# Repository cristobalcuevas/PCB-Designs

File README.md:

<!-- boardrepo-badge:v1 -->

<!-- /boardrepo-badge:v1 -->

# Kicad
Projects with Kicad

### [HornSystem](/HornSystem)

### [LoRaPill](/LoRaPill)

### [PIC18F4550](/PIC18F4550)

### [Shield ESP32](/Shield%20ESP32)

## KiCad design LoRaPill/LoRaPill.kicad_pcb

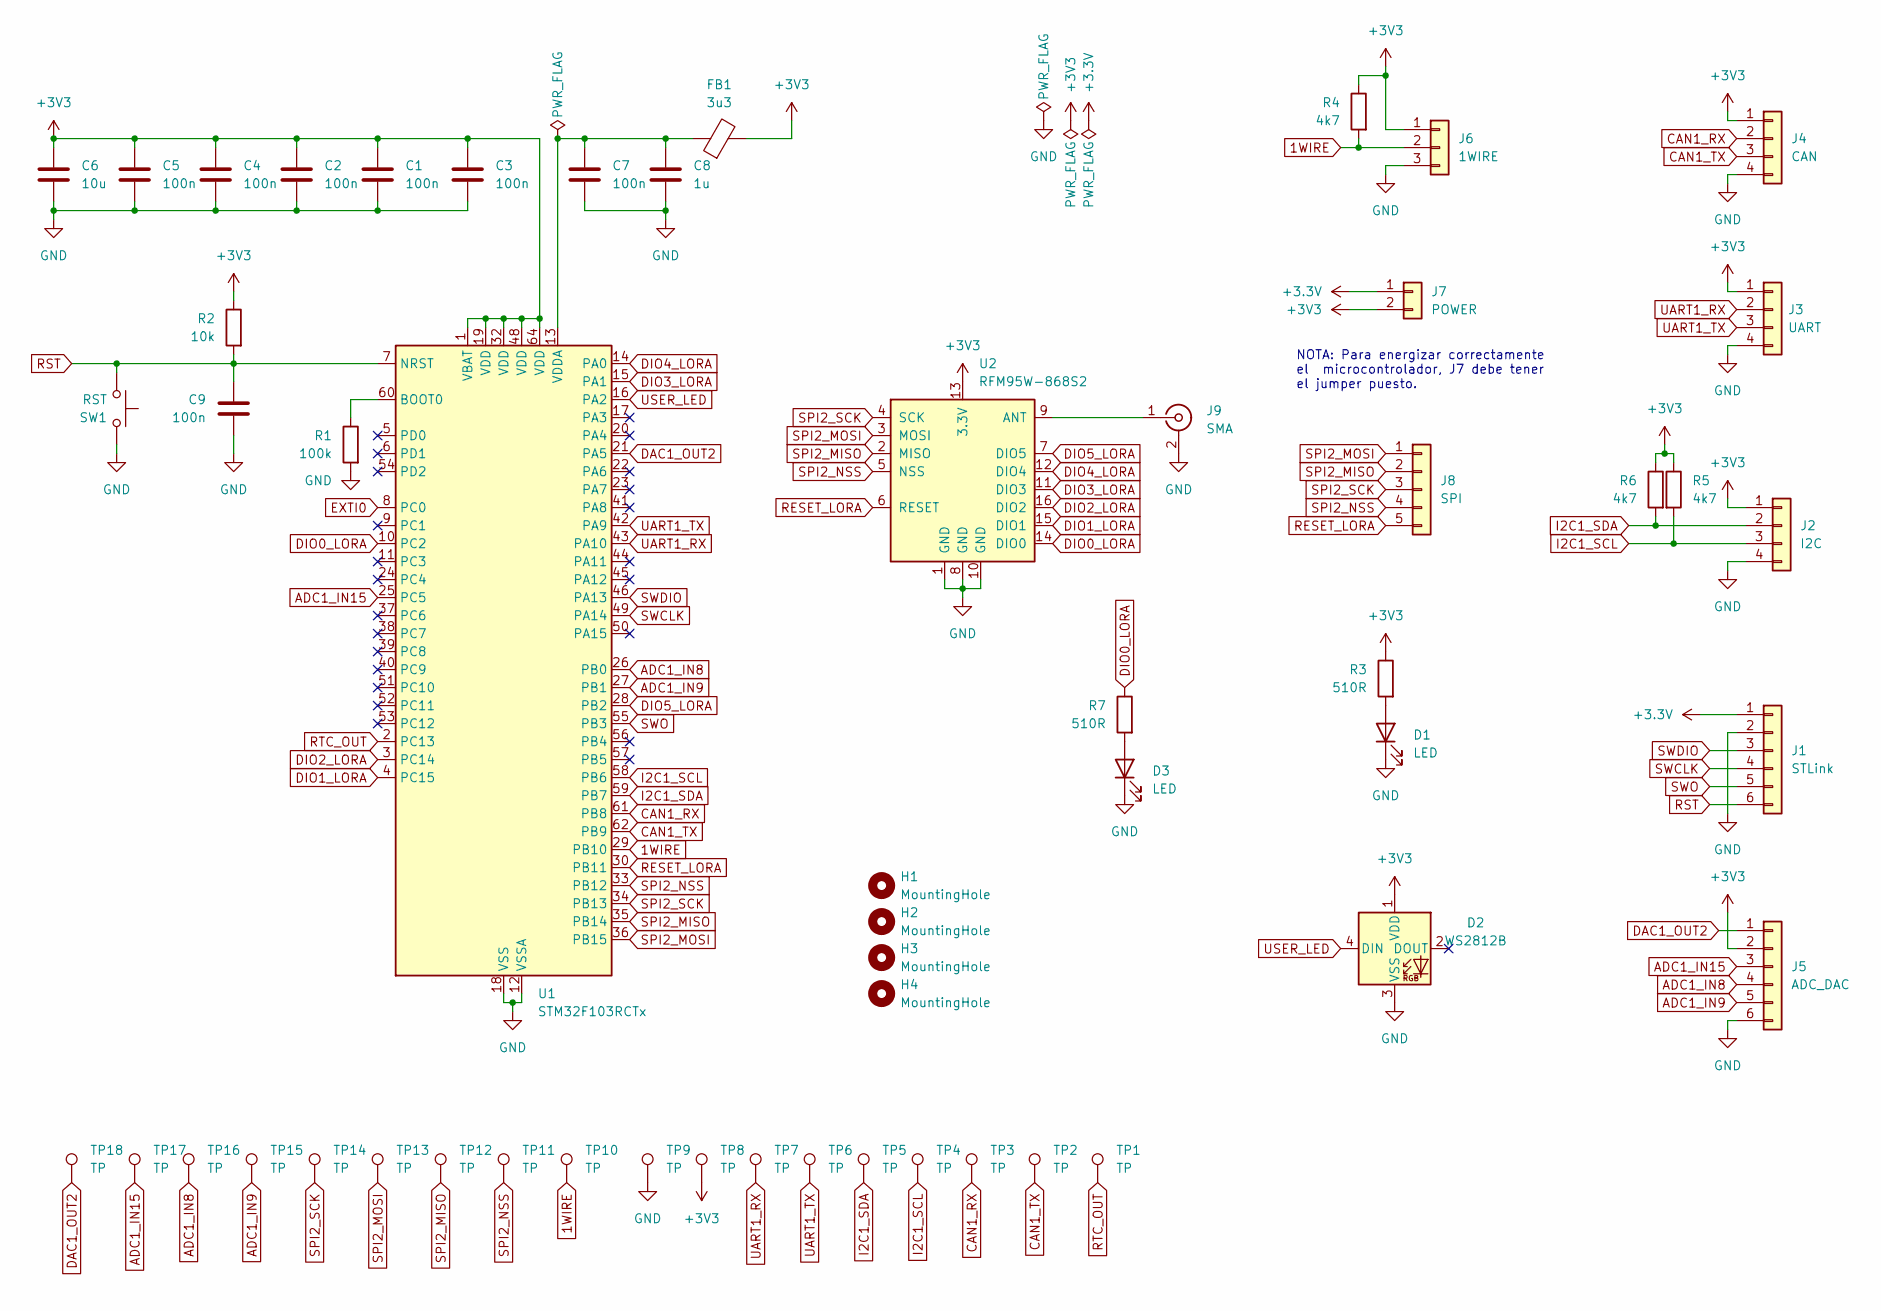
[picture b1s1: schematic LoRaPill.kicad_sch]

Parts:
C1, C2, C3, C4, C5, C7, C9: 100n; C_0805_2012Metric
C6: 10u; C_0805_2012Metric
C8: 1u; C_0805_2012Metric
D1, D3: LED; LED_0805_2012Metric
D2: WS2812B; LED_WS2812B_PLCC4_5.0x5.0mm_P3.2mm
FB1: 3u3; R_0805_2012Metric
H1, H2, H3, H4: MountingHole; MountingHole_3.2mm_M3
J1: STLink; PinHeader_1x06_P2.54mm_Vertical
J2: I2C; PinHeader_1x04_P2.54mm_Vertical
J3: UART; PinHeader_1x04_P2.54mm_Vertical
J4: CAN; PinHeader_1x04_P2.54mm_Vertical
J5: ADC_DAC; PinHeader_1x06_P2.54mm_Vertical
J6: 1WIRE; PinHeader_1x03_P2.54mm_Vertical
J7: POWER; PinHeader_1x02_P2.54mm_Vertical
J8: SPI; PinHeader_1x05_P2.54mm_Vertical
J9: SMA; SMA_Samtec_SMA-J-P-X-ST-EM1_EdgeMount
R1: 100k; R_0805_2012Metric
R2: 10k; R_0805_2012Metric
R3, R7: 510R; R_0805_2012Metric
R4, R5, R6: 4k7; R_0805_2012Metric
SW1: RST; SW_SPST_CK_RS282G05A3
TP1, TP2, TP3, TP4, TP5, TP6, TP7, TP8, TP9, TP10, TP11, TP12, TP13, TP14, TP15, TP16, TP17, TP18: TP; TestPoint_Pad_D1.0mm
U1: STM32F103RCTx; LQFP-64_10x10mm_P0.5mm
U2: RFM95W-868S2; RFM95

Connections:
1WIRE: J6.2, R4.2, TP10.1 (1_1), U1.29 (PB10)
+3.3V: J1.1, J7.1
+3V3: C1.1, C2.1, C3.1, C4.1, C5.1, C6.1, D2.1 (VDD), FB1.2, J2.1, J3.1, J4.1, J5.2, J6.1, J7.2, R2.1, R3.1, R4.1, R5.1, R6.1, TP8.1 (1_1), U1.1 (VBAT), U1.19 (VDD), U1.32 (VDD), U1.48 (VDD), U1.64 (VDD), U2.13 (3.3V)
ADC1_IN8: J5.4, TP16.1 (1_1), U1.26 (PB0)
ADC1_IN9: J5.5, TP15.1 (1_1), U1.27 (PB1)
ADC1_IN15: J5.3, TP17.1 (1_1), U1.25 (PC5)
CAN1_RX: J4.2, TP3.1 (1_1), U1.61 (PB8)
CAN1_TX: J4.3, TP2.1 (1_1), U1.62 (PB9)
DAC1_OUT2: J5.1, TP18.1 (1_1), U1.21 (PA5)
DIO0_LORA: R7.1, U1.10 (PC2), U2.14 (DIO0)
DIO1_LORA: U1.4 (PC15), U2.15 (DIO1)
DIO2_LORA: U1.3 (PC14), U2.16 (DIO2)
DIO3_LORA: U1.15 (PA1), U2.11 (DIO3)
DIO4_LORA: U1.14 (PA0), U2.12 (DIO4)
DIO5_LORA: U1.28 (PB2), U2.7 (DIO5)
EXTI0: U1.8 (PC0)
GND: C1.2, C2.2, C3.2, C4.2, C5.2, C6.2, C7.2, C8.2, C9.2, D1.1 (K), D2.3 (VSS), D3.1 (K), J1.2, J2.4, J3.4, J4.4, J5.6, J6.3, J9.2 (Ext), R1.2, SW1.1, TP9.1 (1_1), U1.12 (VSSA), U1.18 (VSS), U1.31 (VSS), U1.47 (VSS), U1.63 (VSS), U2.1 (GND), U2.8 (GND), U2.10 (GND)
I2C1_SCL: J2.3, R5.2, TP4.1 (1_1), U1.58 (PB6)
I2C1_SDA: J2.2, R6.2, TP5.1 (1_1), U1.59 (PB7)
unnamed: D1.2 (A), R3.2
unnamed: D3.2 (A), R7.2
unnamed: J9.1 (In), U2.9 (ANT)
unnamed: R1.1, U1.60 (BOOT0)
unnamed: C7.1, C8.1, FB1.1, U1.13 (VDDA)
RESET_LORA: J8.5, U1.30 (PB11), U2.6 (RESET)
RST: C9.1, J1.6, R2.2, SW1.2, U1.7 (NRST)
RTC_OUT: TP1.1 (1_1), U1.2 (PC13)
SPI2_MISO: J8.2, TP12.1 (1_1), U1.35 (PB14), U2.2 (MISO)
SPI2_MOSI: J8.1, TP13.1 (1_1), U1.36 (PB15), U2.3 (MOSI)
SPI2_NSS: J8.4, TP11.1 (1_1), U1.33 (PB12), U2.5 (NSS)
SPI2_SCK: J8.3, TP14.1 (1_1), U1.34 (PB13), U2.4 (SCK)
SWCLK: J1.4, U1.49 (PA14)
SWDIO: J1.3, U1.46 (PA13)
SWO: J1.5, U1.55 (PB3)
UART1_RX: J3.2, TP7.1 (1_1), U1.43 (PA10)
UART1_TX: J3.3, TP6.1 (1_1), U1.42 (PA9)
USER_LED: D2.4 (DIN), U1.16 (PA2)

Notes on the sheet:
NOTA: Para energizar correctamente el microcontrolador, J7 debe tener el jumper puesto.

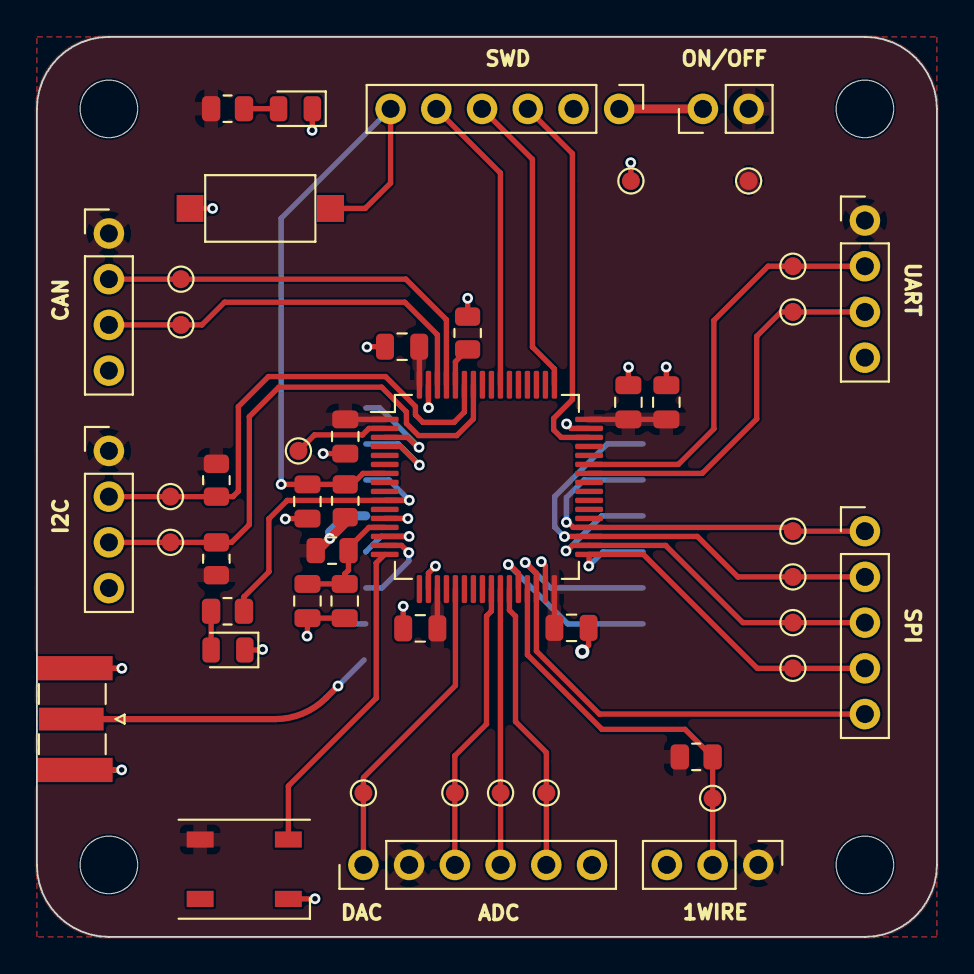
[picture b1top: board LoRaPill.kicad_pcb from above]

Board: 2 copper layers, 50.0 x 50.0 mm, 54 parts (1 on the bottom side), 36 nets.

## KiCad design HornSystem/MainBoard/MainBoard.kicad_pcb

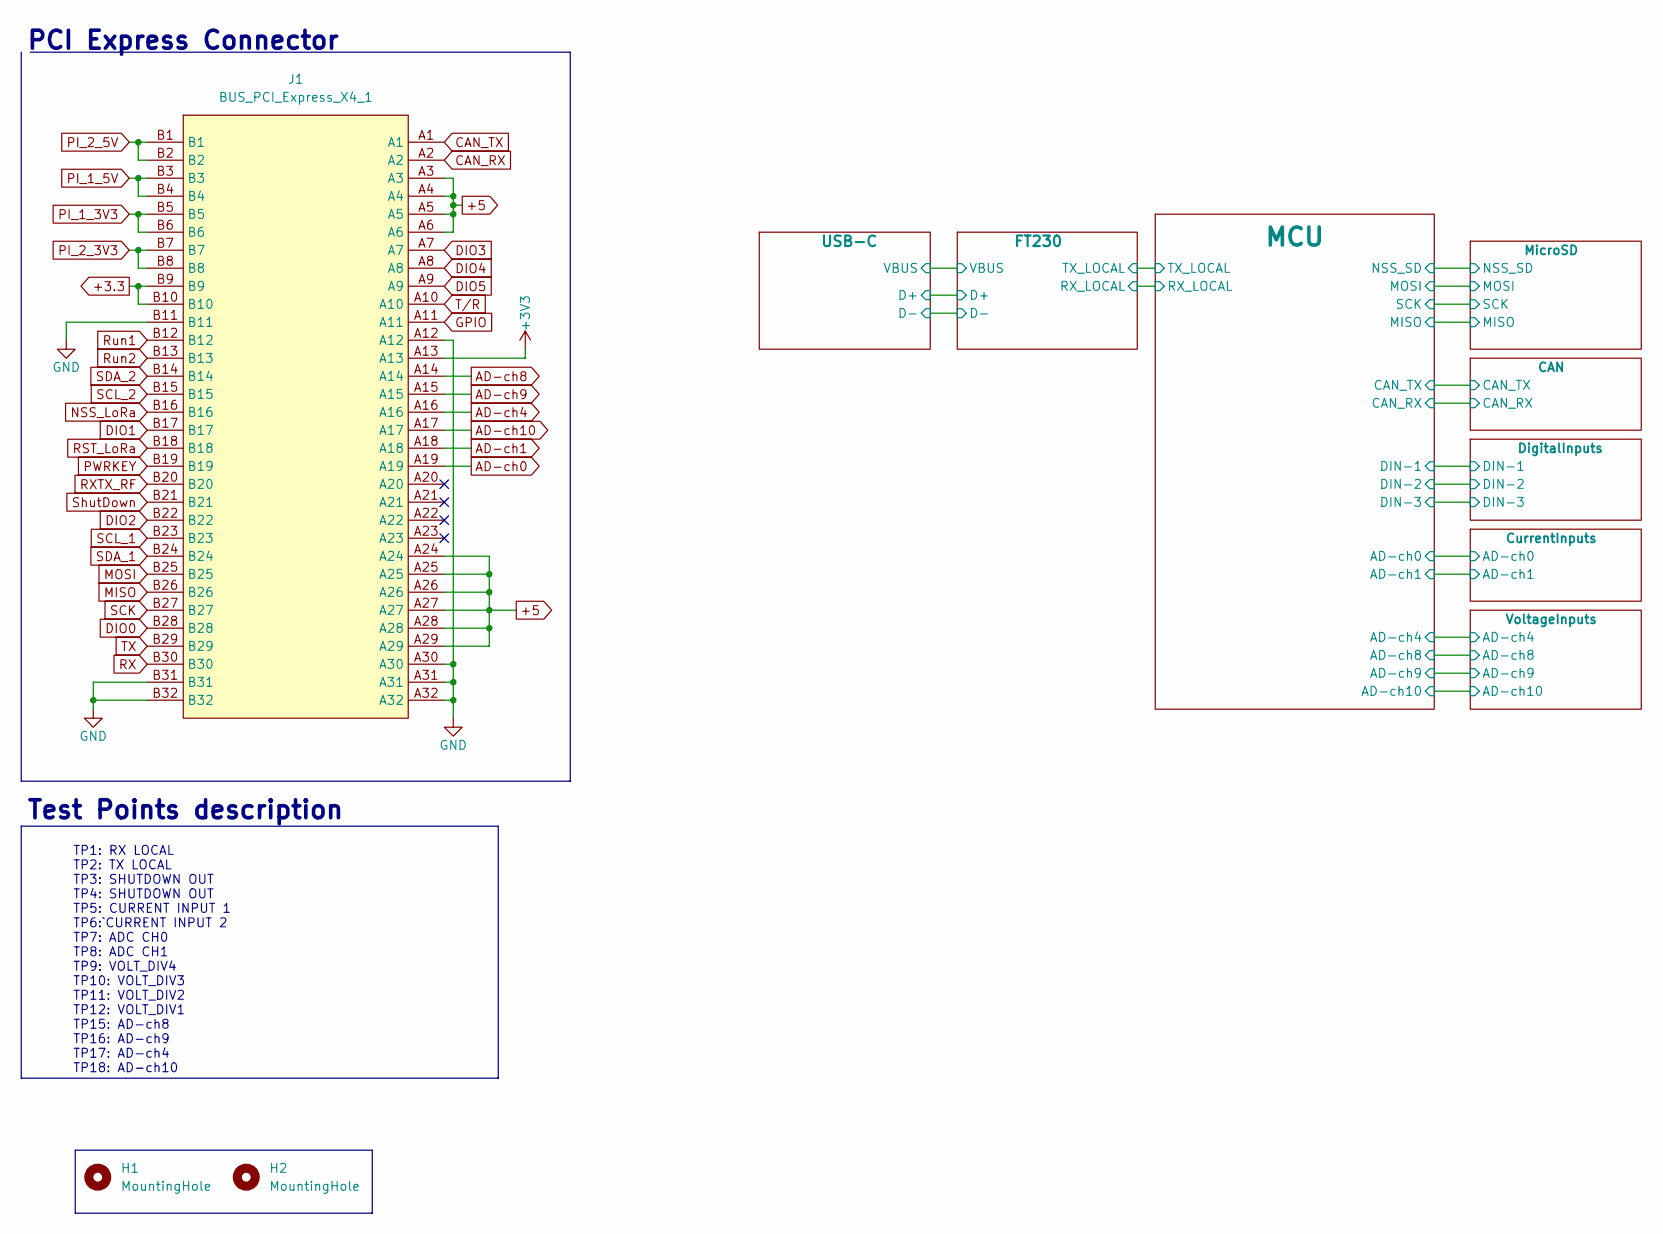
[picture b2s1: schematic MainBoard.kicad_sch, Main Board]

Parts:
H1, H2: MountingHole; MountingHole_3.2mm_M3
J1: BUS_PCI_Express_X4_1; BUS_PCIexpress_x4

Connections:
+3.3: J1.B9, J1.B10; also elsewhere on the board
+3V3: J1.A13; also elsewhere on the board
+5: J1.A3, J1.A4, J1.A5, J1.A6, J1.A24, J1.A25, J1.A26, J1.A27, J1.A28, J1.A29; also elsewhere on the board
AD-ch0: J1.A19; also elsewhere on the board
AD-ch1: J1.A18; also elsewhere on the board
AD-ch4: J1.A16; also elsewhere on the board
AD-ch8: J1.A14; also elsewhere on the board
AD-ch9: J1.A15; also elsewhere on the board
AD-ch10: J1.A17; also elsewhere on the board
CAN_RX: J1.A2; also elsewhere on the board
CAN_TX: J1.A1; also elsewhere on the board
DIO0: J1.B28; also elsewhere on the board
DIO1: J1.B17; also elsewhere on the board
DIO2: J1.B22; also elsewhere on the board
DIO3: J1.A7; also elsewhere on the board
DIO4: J1.A8; also elsewhere on the board
DIO5: J1.A9; also elsewhere on the board
GND: J1.A12, J1.A30, J1.A31, J1.A32, J1.B11, J1.B31, J1.B32; also elsewhere on the board
GPIO: J1.A11; also elsewhere on the board
MISO: J1.B26; also elsewhere on the board
MOSI: J1.B25; also elsewhere on the board
NSS_LoRa: J1.B16; also elsewhere on the board
PI_1_3V3: J1.B5, J1.B6; also elsewhere on the board
PI_1_5V: J1.B3, J1.B4; also elsewhere on the board
PI_2_3V3: J1.B7, J1.B8; also elsewhere on the board
PI_2_5V: J1.B1, J1.B2; also elsewhere on the board
PWRKEY: J1.B19; also elsewhere on the board
RST_LoRa: J1.B18; also elsewhere on the board
RX: J1.B30; also elsewhere on the board
RXTX_RF: J1.B20; also elsewhere on the board
Run1: J1.B12; also elsewhere on the board
Run2: J1.B13; also elsewhere on the board
SCK: J1.B27; also elsewhere on the board
SCL_1: J1.B23; also elsewhere on the board
SCL_2: J1.B15; also elsewhere on the board
SDA_1: J1.B24; also elsewhere on the board
SDA_2: J1.B14; also elsewhere on the board
ShutDown: J1.B21; also elsewhere on the board
TX: J1.B29; also elsewhere on the board
T/R: J1.A10; also elsewhere on the board

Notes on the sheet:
PCI Express Connector
Test Points description
TP1: RX LOCAL TP2: TX LOCAL TP3: SHUTDOWN OUT TP4: SHUTDOWN OUT TP5: CURRENT INPUT 1 TP6:`CURRENT INPUT 2 TP7: ADC CH0 TP8: ADC CH1 TP9: VOLT_DIV4 TP10: VOLT_DIV3 TP11: VOLT_DIV2 TP12: VOLT_DIV1 TP15: AD-ch8 TP16: AD-ch9 TP17: AD-ch4 TP18: AD-ch10

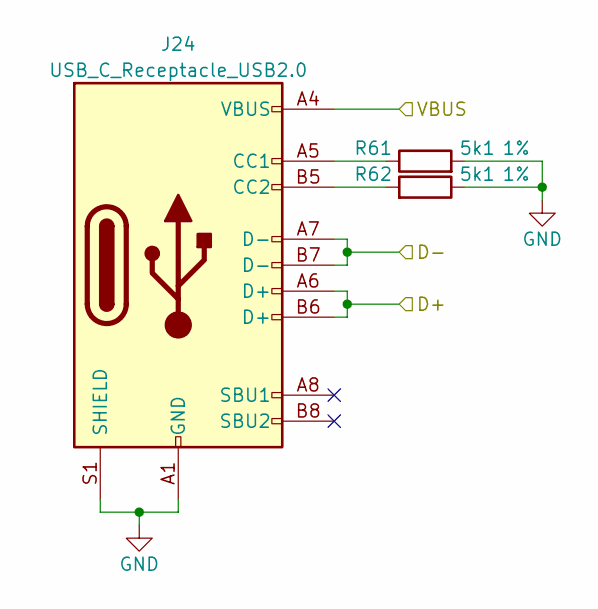
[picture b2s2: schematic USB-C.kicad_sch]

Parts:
J24: USB_C_Receptacle_USB2.0; USB_C_Receptacle_GCT_USB4105-xx-A_16P_TopMnt_Horizontal; JLCPCB Part C2988369
R61, R62: 5k1; R_0805_2012Metric; Tolerance 1%; JLCPCB Part C118848

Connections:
/FT230/D+: J24.A6 (D+), J24.B6 (D+); also elsewhere on the board
/FT230/D-: J24.A7 (D-), J24.B7 (D-); also elsewhere on the board
/FT230/VBUS: J24.A4 (VBUS), J24.A9 (VBUS), J24.B4 (VBUS), J24.B9 (VBUS); also elsewhere on the board
GND: J24.A1 (GND), J24.A12 (GND), J24.B1 (GND), J24.B12 (GND), J24.S1 (SHIELD), R61.2, R62.1; also elsewhere on the board
unnamed: J24.A5 (CC1), R61.1
unnamed: J24.B5 (CC2), R62.2

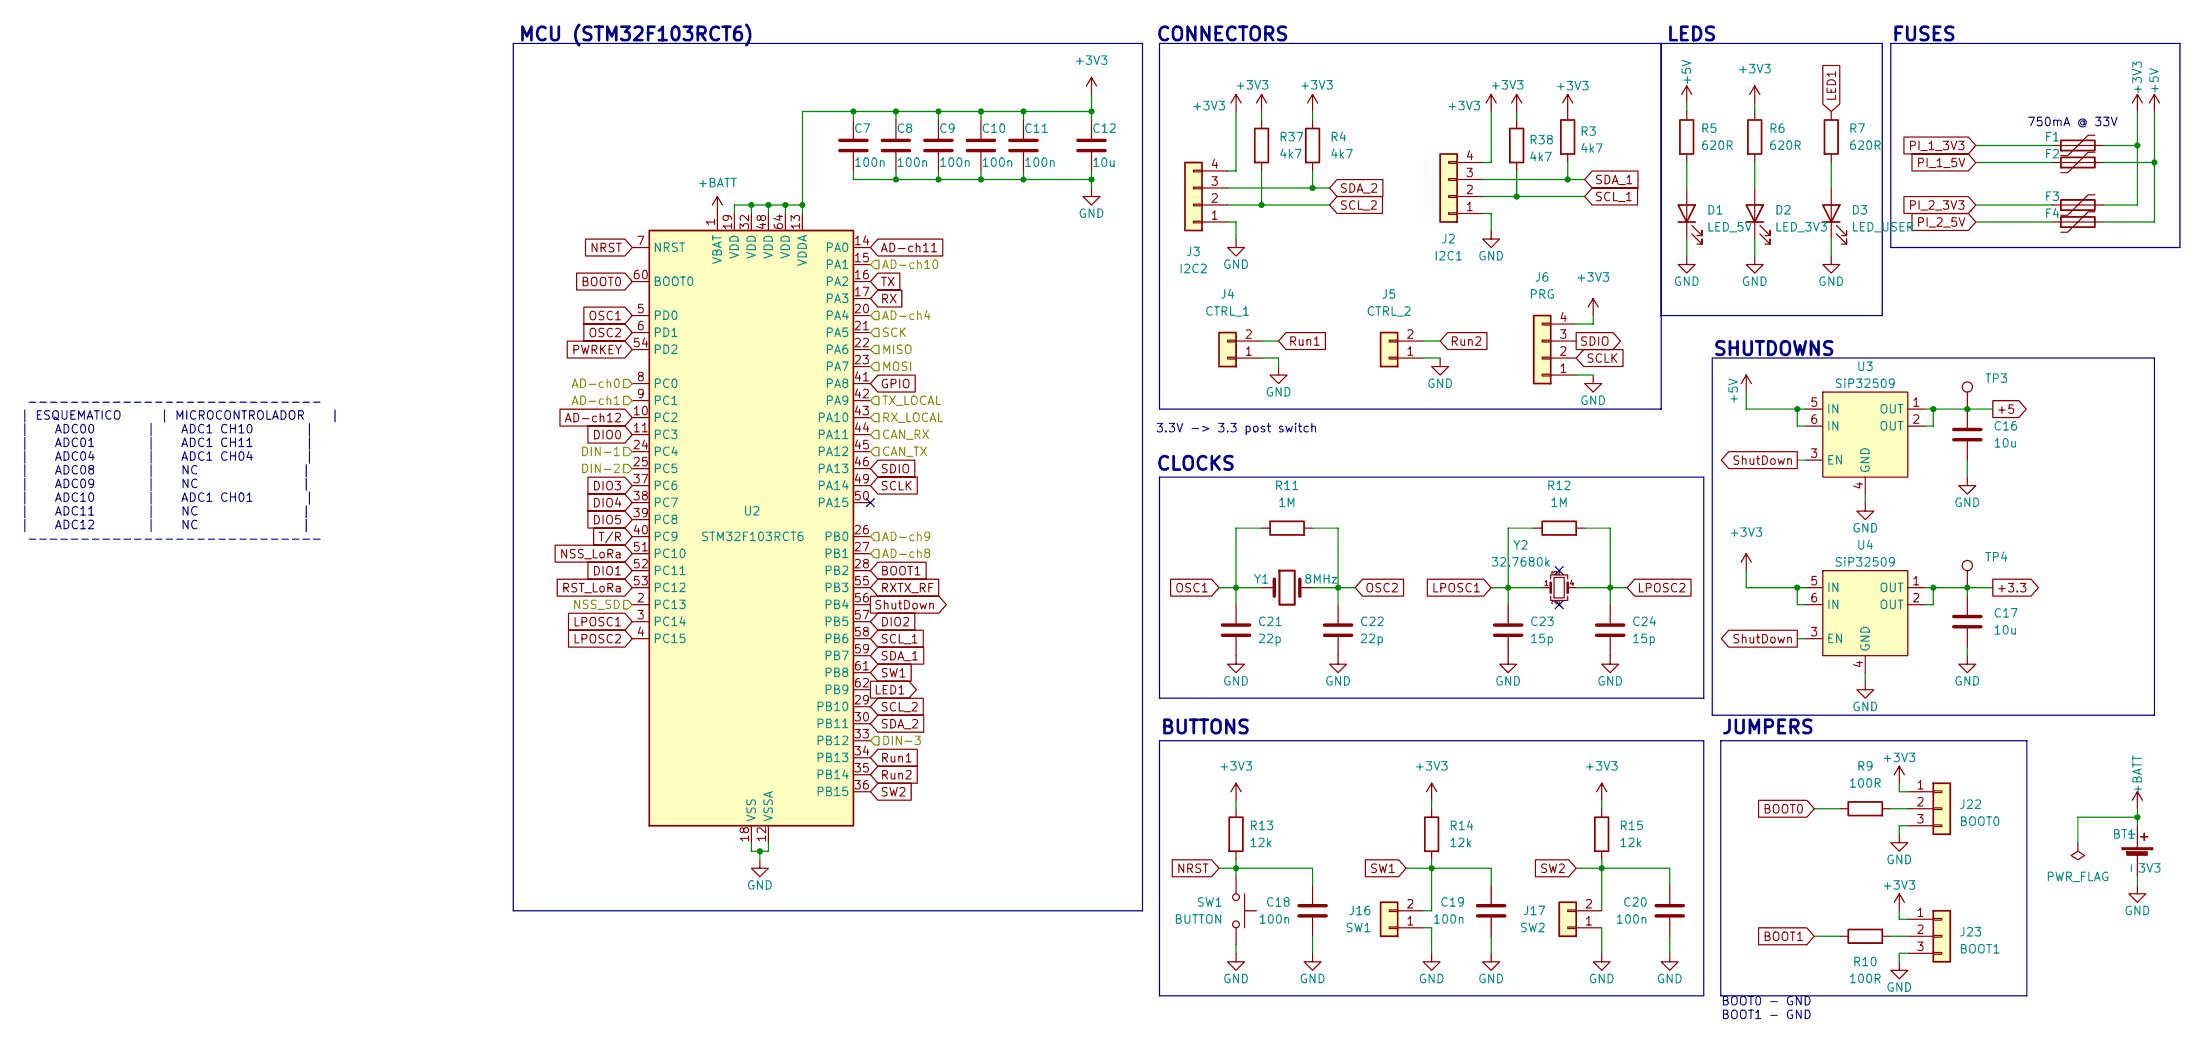
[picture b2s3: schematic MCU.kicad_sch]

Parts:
BT1: 3V3; BAT_BH32T-C-G; Digikey Part BH32T-C-G
C7, C8, C9, C10, C11, C18, C19, C20: 100n; C_0805_2012Metric; JLCPCB Part C710457
C12, C16, C17: 10u; C_0805_2012Metric; JLCPCB Part C380331
C21, C22: 22p; C_0805_2012Metric; JLCPCB Part C376875
C23, C24: 15p; C_0805_2012Metric; JLCPCB Part C525285
D1: LED_5V; LED_0805_2012Metric; JLCPCB Part C84256
D2: LED_3V3; LED_0805_2012Metric; JLCPCB Part C434435
D3: LED_USER; LED_0805_2012Metric; JLCPCB Part C434435
F1, F2, F3, F4: Polyfuse; Fuse_1812_4532Metric; JLCPCB Part C220153
J2: I2C1; PinHeader_1x04_P2.54mm_Vertical
J3: I2C2; PinHeader_1x04_P2.54mm_Vertical
J4: CTRL_1; PinHeader_1x02_P2.54mm_Vertical
J5: CTRL_2; PinHeader_1x02_P2.54mm_Vertical
J6: PRG; PinHeader_1x04_P2.54mm_Vertical
J16: SW1; PinHeader_1x02_P2.54mm_Vertical
J17: SW2; PinHeader_1x02_P2.54mm_Vertical
J22: BOOT0; PinHeader_1x03_P2.54mm_Vertical
J23: BOOT1; PinHeader_1x03_P2.54mm_Vertical
R3, R4, R37, R38: 4k7; R_0805_2012Metric; JLCPCB Part C2759288
R5, R6, R7: 620R; R_0805_2012Metric; JLCPCB Part C139852
R9, R10: 100R; R_0805_2012Metric; JLCPCB Part C414981
R11, R12: 1M; R_0805_2012Metric; JLCPCB Part C136578
R13, R14, R15: 12k; R_0805_2012Metric; JLCPCB Part C114556
SW1: BUTTON; SW_SPST_TL3305A; JLCPCB Part C2886899
TP3, TP4: TestPoint; TestPoint_Pad_D1.0mm
U2: STM32F103RCT6; LQFP-64_10x10mm_P0.5mm; JLCPCB Part C39704
U3, U4: SiP32509; TSOT-23-6; JLCPCB Part C335619
Y1: 8MHz; Crystal_HC18-U_Vertical; JLCPCB Part C700809
Y2: 32.7680k; Crystal_SMD_SeikoEpson_MC306-4Pin_8.0x3.2mm; JLCPCB Part C2650464

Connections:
+3.3: C17.1, TP4.1, U4.1 (OUT), U4.2 (OUT); also elsewhere on the board
+3V3: C7.1, C8.1, C9.1, C10.1, C11.1, C12.1, F1.2, F3.2, J2.4, J3.4, J6.4, J22.1, J23.1, R3.1, R4.1, R6.1, R13.1, R14.1, R15.1, R37.1, R38.1, U2.13 (VDDA), U2.19 (VDD), U2.32 (VDD), U2.48 (VDD), U2.64 (VDD), U4.5 (IN), U4.6 (IN); also elsewhere on the board
+5: C16.1, TP3.1, U3.1 (OUT), U3.2 (OUT); also elsewhere on the board
+5V: F2.2, F4.2, R5.1, U3.5 (IN), U3.6 (IN); also elsewhere on the board
+BATT: BT1.1 (+), U2.1 (VBAT)
/DigitalInputs/DIN-1: U2.24 (PC4); also elsewhere on the board
/DigitalInputs/DIN-2: U2.25 (PC5); also elsewhere on the board
/DigitalInputs/DIN-3: U2.33 (PB12); also elsewhere on the board
/FT230/RX_LOCAL: U2.43 (PA10); also elsewhere on the board
/FT230/TX_LOCAL: U2.42 (PA9); also elsewhere on the board
/MCU/NSS_SD: U2.2 (PC13); also elsewhere on the board
AD-ch0: U2.8 (PC0); also elsewhere on the board
AD-ch1: U2.9 (PC1); also elsewhere on the board
AD-ch4: U2.20 (PA4); also elsewhere on the board
AD-ch8: U2.27 (PB1); also elsewhere on the board
AD-ch9: U2.26 (PB0); also elsewhere on the board
AD-ch10: U2.15 (PA1); also elsewhere on the board
AD-ch11: U2.14 (PA0)
AD-ch12: U2.10 (PC2)
BOOT0: R9.1, U2.60 (BOOT0)
BOOT1: R10.1, U2.28 (PB2)
CAN_RX: U2.44 (PA11); also elsewhere on the board
CAN_TX: U2.45 (PA12); also elsewhere on the board
DIO0: U2.11 (PC3); also elsewhere on the board
DIO1: U2.52 (PC11); also elsewhere on the board
DIO2: U2.57 (PB5); also elsewhere on the board
DIO3: U2.37 (PC6); also elsewhere on the board
DIO4: U2.38 (PC7); also elsewhere on the board
DIO5: U2.39 (PC8); also elsewhere on the board
GND: BT1.2 (-), C7.2, C8.2, C9.2, C10.2, C11.2, C12.2, C16.2, C17.2, C18.1, C19.1, C20.1, C21.2, C22.2, C23.2, C24.2, D1.1 (K), D2.1 (K), D3.1 (K), J2.1, J3.1, J4.1, J5.1, J6.1, J16.1, J17.1, J22.3, J23.3, SW1.1, U2.12 (VSSA), U2.18 (VSS), U2.31 (VSS), U2.47 (VSS), U2.63 (VSS), U3.4 (GND), U4.4 (GND); also elsewhere on the board
GPIO: U2.41 (PA8); also elsewhere on the board
LED1: R7.1, U2.62 (PB9)
LPOSC1: C23.1, R12.1, U2.3 (PC14), Y2.1
LPOSC2: C24.1, R12.2, U2.4 (PC15), Y2.4
MISO: U2.22 (PA6); also elsewhere on the board
MOSI: U2.23 (PA7); also elsewhere on the board
NRST: C18.2, R13.2, SW1.2, U2.7 (NRST)
NSS_LoRa: U2.51 (PC10); also elsewhere on the board
unnamed: D1.2 (A), R5.2
unnamed: D2.2 (A), R6.2
unnamed: D3.2 (A), R7.2
unnamed: J22.2, R9.2
unnamed: J23.2, R10.2
OSC1: C21.1, R11.1, U2.5 (PD0), Y1.1
OSC2: C22.1, R11.2, U2.6 (PD1), Y1.2
PI_1_3V3: F1.1; also elsewhere on the board
PI_1_5V: F2.1; also elsewhere on the board
PI_2_3V3: F3.1; also elsewhere on the board
PI_2_5V: F4.1; also elsewhere on the board
PWRKEY: U2.54 (PD2); also elsewhere on the board
RST_LoRa: U2.53 (PC12); also elsewhere on the board
RX: U2.17 (PA3); also elsewhere on the board
RXTX_RF: U2.55 (PB3); also elsewhere on the board
Run1: J4.2, U2.34 (PB13); also elsewhere on the board
Run2: J5.2, U2.35 (PB14); also elsewhere on the board
SCK: U2.21 (PA5); also elsewhere on the board
SCLK: J6.2, U2.49 (PA14)
SCL_1: J2.2, R38.2, U2.58 (PB6); also elsewhere on the board
SCL_2: J3.2, R37.2, U2.29 (PB10); also elsewhere on the board
SDA_1: J2.3, R3.2, U2.59 (PB7); also elsewhere on the board
SDA_2: J3.3, R4.2, U2.30 (PB11); also elsewhere on the board
SDIO: J6.3, U2.46 (PA13)
SW1: C19.2, J16.2, R14.2, U2.61 (PB8)
SW2: C20.2, J17.2, R15.2, U2.36 (PB15)
ShutDown: U2.56 (PB4), U3.3 (EN), U4.3 (EN); also elsewhere on the board
TX: U2.16 (PA2); also elsewhere on the board
T/R: U2.40 (PC9); also elsewhere on the board

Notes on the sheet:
MCU (STM32F103RCT6)
CONNECTORS
3.3V -> 3.3 post switch
BOOT0 - GND BOOT1 - GND
CLOCKS
---------------------------- | ESQUEMATICO | MICROCONTROLADOR | | ADC00 | ADC1 CH10 | | ADC01 | ADC1 CH11 | | ADC04 | ADC1 CH04 | | ADC08 | NC | | ADC09 | NC | | ADC10 | ADC1 CH01 | | ADC11 | NC | | ADC12 | NC | ----------------------------
750mA @ 33V
FUSES
BUTTONS
SHUTDOWNS
JUMPERS
LEDS

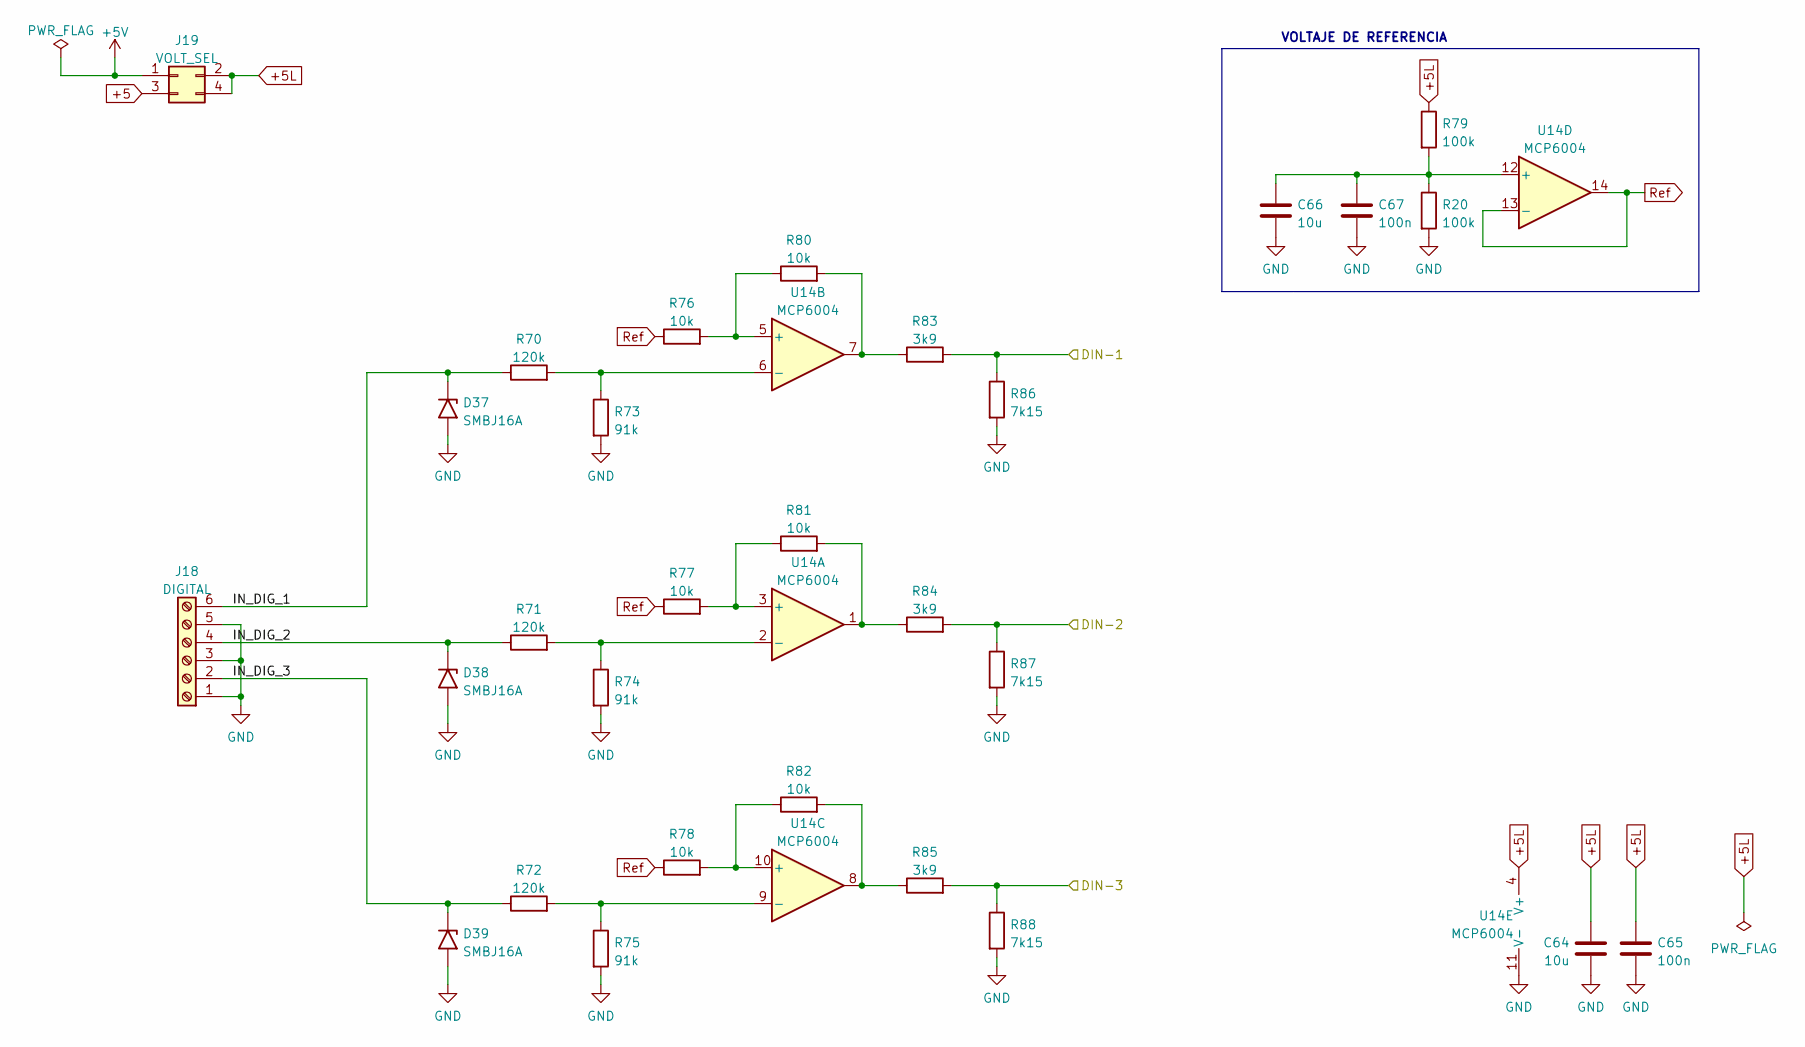
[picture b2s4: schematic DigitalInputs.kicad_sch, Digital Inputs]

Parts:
C64, C66: 10u; C_0805_2012Metric; JLCPCB Part C380331
C65, C67: 100n; C_0805_2012Metric; JLCPCB Part C710457
D37, D38, D39: SMBJ16A; D_SMB; JLCPCB Part C2848701
J18: DIGITAL; PinHeader_1x06_P2.54mm_Vertical
J19: VOLT_SEL; PinHeader_2x02_P2.54mm_Vertical
R20, R79: 100k; R_0805_2012Metric; JLCPCB Part C149504
R70, R71, R72: 120k; R_0805_2012Metric; JLCPCB Part C294681
R73, R74, R75: 91k; R_0805_2012Metric; JLCPCB Part C286618
R76, R77, R78, R80, R81, R82: 10k; R_0805_2012Metric; JLCPCB Part C212284
R83, R84, R85: 3k9; R_0805_2012Metric; JLCPCB Part C139889
R86, R87, R88: 7k15; R_0805_2012Metric; JLCPCB Part C104487
U14: MCP6004; TSSOP-14_4.4x5mm_P0.65mm; JLCPCB Part C50282

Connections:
+5: J19.3; also elsewhere on the board
+5L: C64.1, C65.1, J19.2, J19.4, R79.1, U14.4 (V+)
+5V: J19.1; also elsewhere on the board
/DigitalInputs/DIN-1: R83.2, R86.1; also elsewhere on the board
/DigitalInputs/DIN-2: R84.2, R87.1; also elsewhere on the board
/DigitalInputs/DIN-3: R85.2, R88.1; also elsewhere on the board
/DigitalInputs/IN_DIG_1: D37.1 (A1), J18.6, R70.1
/DigitalInputs/IN_DIG_2: D38.1 (A1), J18.4, R71.1
/DigitalInputs/IN_DIG_3: D39.1 (A1), J18.2, R72.1
GND: C64.2, C65.2, C66.2, C67.2, D37.2 (A2), D38.2 (A2), D39.2 (A2), J18.1, J18.3, J18.5, R20.2, R73.2, R74.2, R75.2, R86.2, R87.2, R88.2, U14.11 (V-); also elsewhere on the board
unnamed: R80.2, R83.1, U14.7
unnamed: R81.2, R84.1, U14.1
unnamed: R82.2, R85.1, U14.8
unnamed: R77.2, R81.1, U14.3 (+)
unnamed: R71.2, R74.1, U14.2 (-)
unnamed: R76.2, R80.1, U14.5 (+)
unnamed: R70.2, R73.1, U14.6 (-)
unnamed: R78.2, R82.1, U14.10 (+)
unnamed: R72.2, R75.1, U14.9 (-)
unnamed: C66.1, C67.1, R20.1, R79.2, U14.12 (+)
Ref: R76.1, R77.1, R78.1, U14.13 (-), U14.14

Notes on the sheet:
VOLTAJE DE REFERENCIA

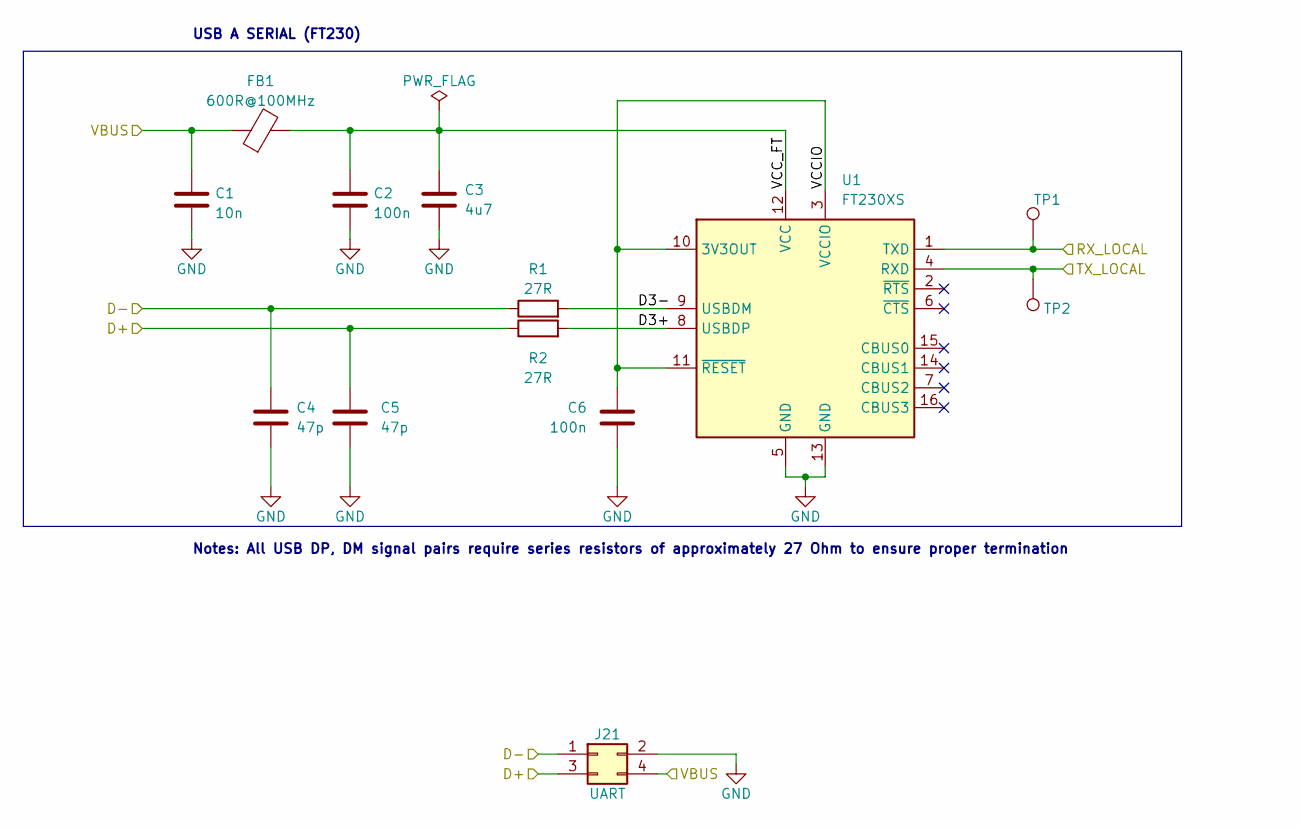
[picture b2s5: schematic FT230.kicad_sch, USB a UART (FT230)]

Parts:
C1: 10n; C_0805_2012Metric; JLCPCB Part C282724
C2, C6: 100n; C_0805_2012Metric; JLCPCB Part C710457
C3: 4u7; C_0805_2012Metric; JLCPCB Part C513770
C4, C5: 47p; C_0805_2012Metric; JLCPCB Part C24659
FB1: 600R@100MHz; L_0805_2012Metric; JLCPCB Part C2661781
J21: UART; PinHeader_2x02_P2.54mm_Vertical
R1, R2: 27R; R_0805_2012Metric; JLCPCB Part C2889599
TP1, TP2: TestPoint; TestPoint_Pad_D1.0mm
U1: FT230XS; SSOP-16_3.9x4.9mm_P0.635mm; JLCPCB Part C69082

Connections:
/FT230/D3+: R2.2, U1.8 (USBDP)
/FT230/D3-: R1.2, U1.9 (USBDM)
/FT230/D+: C5.1, J21.3, R2.1; also elsewhere on the board
/FT230/D-: C4.1, J21.1, R1.1; also elsewhere on the board
/FT230/RX_LOCAL: TP1.1, U1.1 (TXD); also elsewhere on the board
/FT230/TX_LOCAL: TP2.1, U1.4 (RXD); also elsewhere on the board
/FT230/VBUS: C1.1, FB1.1, J21.4; also elsewhere on the board
/FT230/VCCIO: C6.1, U1.3 (VCCIO), U1.10 (3V3OUT), U1.11 (~RESET)
/FT230/VCC_FT: C2.1, C3.1, FB1.2, U1.12 (VCC)
GND: C1.2, C2.2, C3.2, C4.2, C5.2, C6.2, J21.2, U1.5 (GND), U1.13 (GND); also elsewhere on the board

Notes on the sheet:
USB A SERIAL (FT230)
Notes: All USB DP, DM signal pairs require series resistors of approximately 27 Ohm to ensure proper termination
